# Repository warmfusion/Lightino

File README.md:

**Lightino STEAM Fidget Spinner**

For more details, check out the product page at

http://makerstorage.com/index.php?id_product=29&controller=product

MakerStorage invests time and resources providing this open source design, please support MakerStorage and open-source hardware by purchasing products from MakerStorage!

Designed by MakerStorage LLC.

Creative Commons Attribution, Share-Alike license, check https://creativecommons.org/licenses/by-sa/3.0/ for more information All text above must be included in any redistribution

I am thinking for a while about how to teach young generation coding funnily. We all know it is essential to learn how to code, but it is not so easy. It takes time, and most of the young learners give up and fail at the beginning. You need something interesting to continue and try many times even you fail one after the other. It requires more time and practice than you might expect, so you need a feedback mechanism that motivates you on trying without giving up. It is an absolute truth that Fidget Spinners finds its way into the hearts of young people. I decided to use this popularity and create a fidget spinner with RGB LEDs and Arduino. It was a combination of two things that I love the most.

Our Blog for code sharing: https://lightino.org/

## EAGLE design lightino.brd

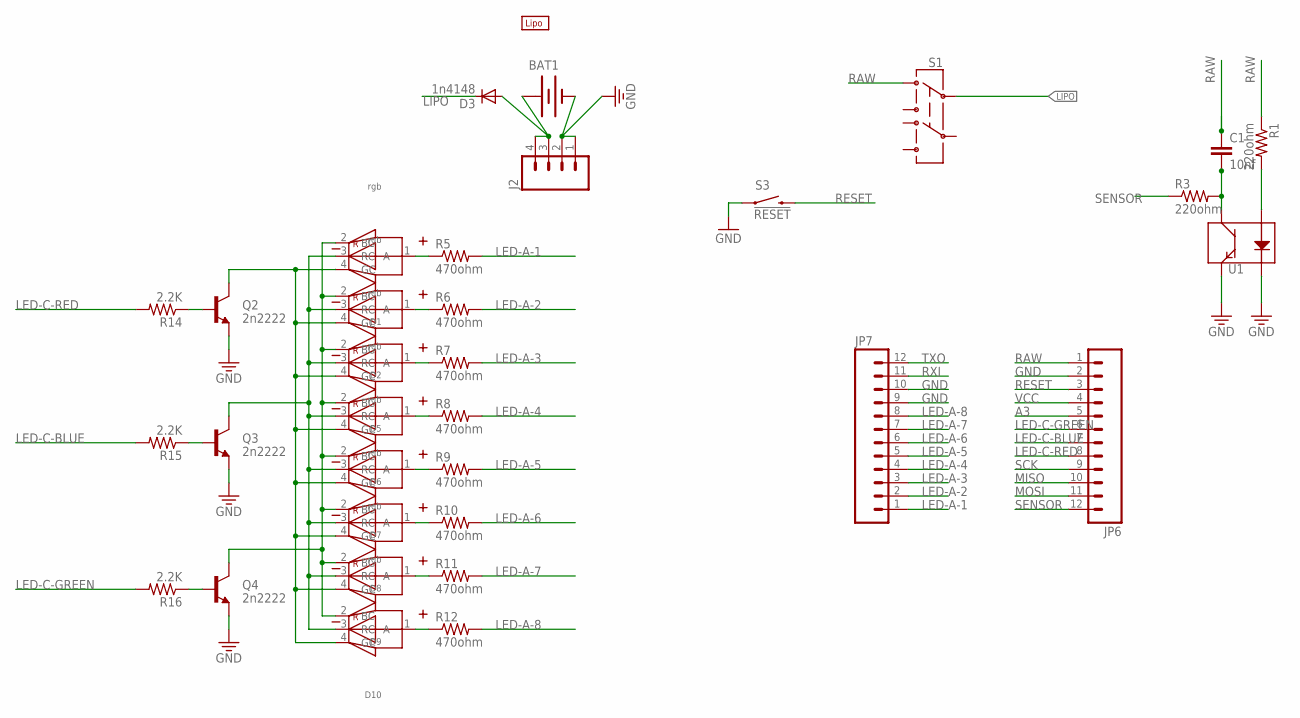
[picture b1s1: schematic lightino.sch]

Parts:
BAT1: BATTERYLIPO-TABS; LIPO-110-TABS
C1: 10nf; 0805
D1, D2, D5, D6, D7, D8, D9, D10: rgb; 3528-COMMON-ANODE
D3: 1n4148; SOD-323
J2: M041.27MM; 1X04-1.27MM
JP6, JP7: M12PTH; 1X12
Q2, Q3, Q4: 2n2222; SOT23
R1, R3: 220ohm; M0805
R5, R6, R7, R8, R9, R10, R11, R12: 470ohm; M0805
R14, R15, R16: 2.2K; M0805
S1: SWITCH-DPDTAYZ0202; AYZ0202
S3: !RESET; TACTILE_SWITCH_SMD
U1: QRE1113SMD-W; QRE1113-W
U$1: LIPO-OUTLINE100; LIPO-100

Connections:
A3: JP6.5
GND: BAT1.-, J2.1, J2.2, JP6.2, JP7.9, JP7.10, Q2.2 (E), Q3.2 (E), Q4.2 (E), S3.1, U1.2 (K), U1.4 (E)
LED-A-1: JP7.1, R5.2
LED-A-2: JP7.2, R6.2
LED-A-3: JP7.3, R7.2
LED-A-4: JP7.4, R8.2
LED-A-5: JP7.5, R9.2
LED-A-6: JP7.6, R10.2
LED-A-7: JP7.7, R11.2
LED-A-8: JP7.8, R12.2
LED-C-BLUE: JP6.7, R15.2
LED-C-GREEN: JP6.6, R16.2
LED-C-RED: JP6.8, R14.2
LIPO: D3.1 (C), S1.2
MISO: JP6.10
MOSI: JP6.11
unnamed: BAT1.+, D3.2 (A), J2.3, J2.4
unnamed: R1.2, U1.1 (A)
unnamed: D2.1 (A), R6.1
unnamed: D1.1 (A), R5.1
unnamed: D10.1 (A), R12.1
unnamed: D9.1 (A), R11.1
unnamed: D8.1 (A), R10.1
unnamed: D7.1 (A), R9.1
unnamed: D6.1 (A), R8.1
unnamed: D5.1 (A), R7.1
unnamed: D1.2 (BC), D2.2 (BC), D5.2 (BC), D6.2 (BC), D7.2 (BC), D8.2 (BC), D9.2 (BC), D10.2 (BC), Q4.3 (C)
unnamed: D1.3 (RC), D2.3 (RC), D5.3 (RC), D6.3 (RC), D7.3 (RC), D8.3 (RC), D9.3 (RC), D10.3 (RC), Q3.3 (C)
unnamed: D1.4 (GC), D2.4 (GC), D5.4 (GC), D6.4 (GC), D7.4 (GC), D8.4 (GC), D9.4 (GC), D10.4 (GC), Q2.3 (C)
unnamed: Q2.1 (B), R14.1
unnamed: Q3.1 (B), R15.1
unnamed: Q4.1 (B), R16.1
RAW: C1.1, JP6.1, R1.1, S1.1
RESET: JP6.3, S3.3 (2)
RXI: JP7.11
SCK: JP6.9
SENSOR: JP6.12, R3.1
TXO: JP7.12
VCC: JP6.4
XX: C1.2, R3.2, U1.3 (C)

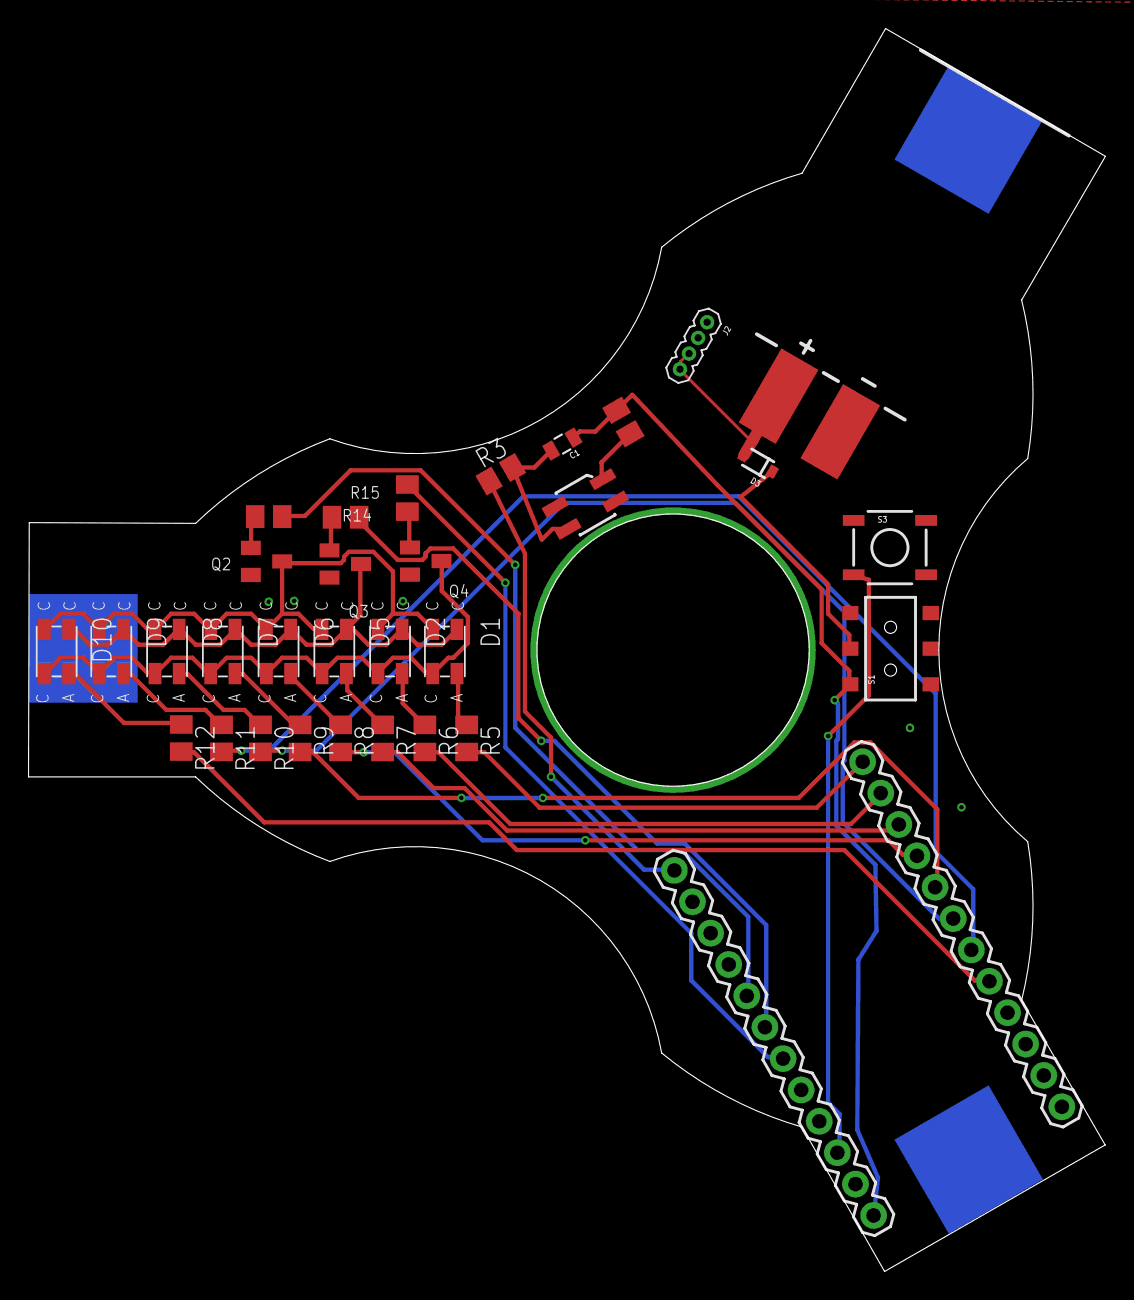
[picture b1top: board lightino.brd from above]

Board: 2 copper layers, 75.5 x 87.2 mm, 34 parts (0 on the bottom side), 33 nets.

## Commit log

2017-08-21 examples
2017-09-29 Spinner Cap
2018-04-12 Added some instruction for getting started to the readme

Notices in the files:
parts and their libraries:
Wurth_Elektronik_Optoelectronics_rev15b: Copyright: Würth Elektronik
SparkFun-Electromechanical: Licensing: Creative Commons ShareAlike 4.0 International - https://creativecommons.org/licenses/by-sa/4.0
